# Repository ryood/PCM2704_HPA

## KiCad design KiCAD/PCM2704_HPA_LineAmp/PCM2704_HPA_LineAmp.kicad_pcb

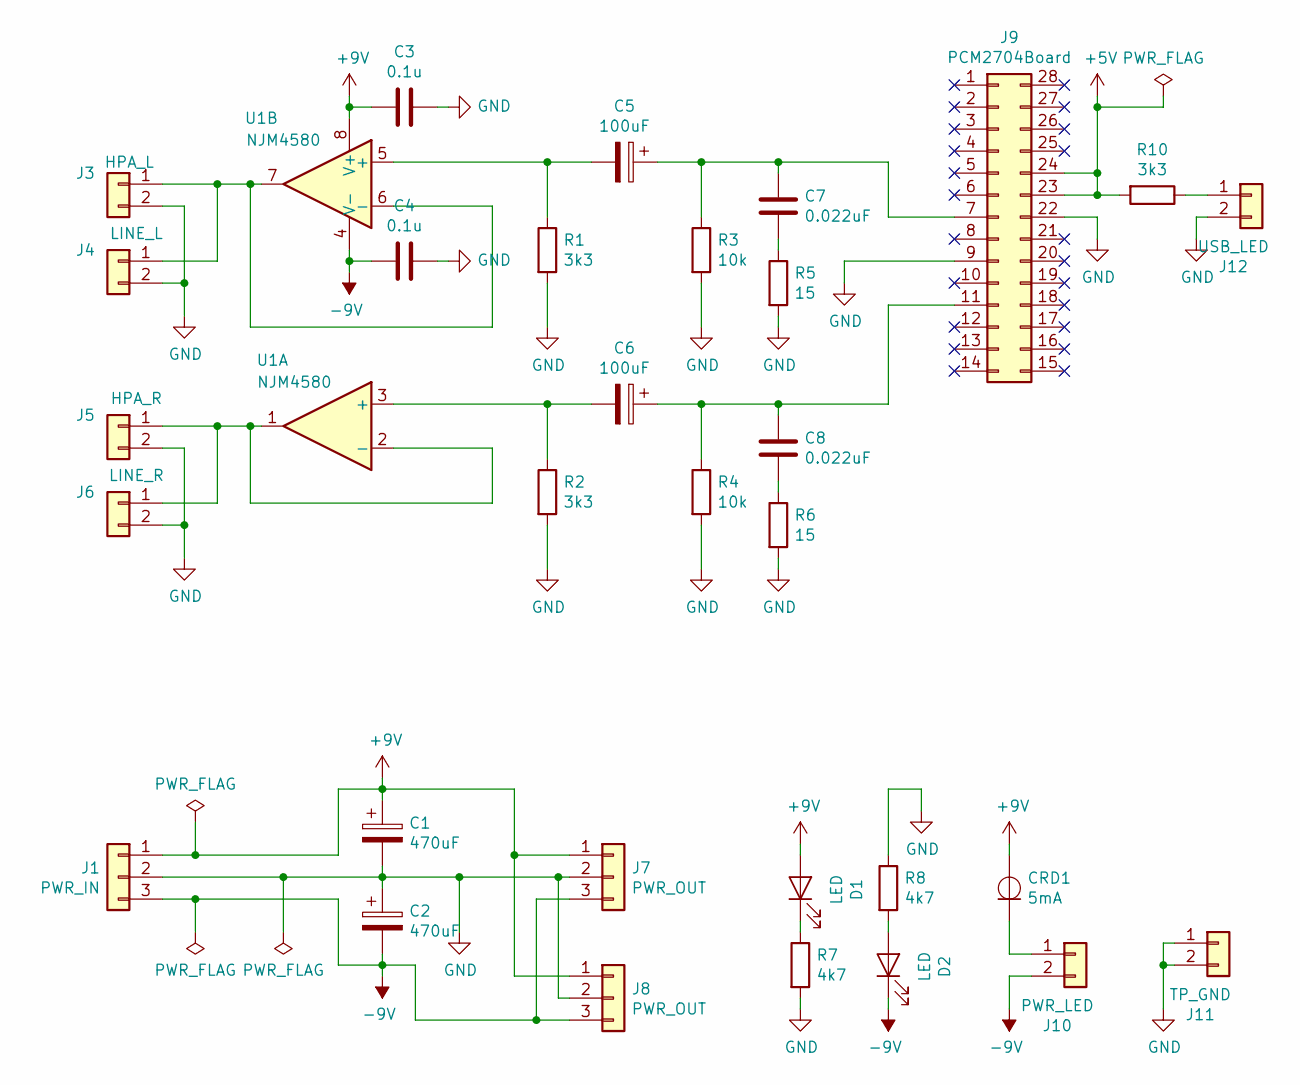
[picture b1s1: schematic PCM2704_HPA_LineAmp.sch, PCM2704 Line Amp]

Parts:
C1, C2: 470uF; CP_Radial_D10.0mm_P5.00mm
C3: 0.1u; C_Disc_D3.0mm_W1.6mm_P2.50mm
C4: 0.1u; C_Disc_D4.3mm_W1.9mm_P5.00mm
C5, C6: 100uF; CP_Radial_D7.5mm_P2.50mm
C7, C8: 0.022uF; C_Rect_L7.0mm_W2.0mm_P5.00mm
CRD1: 5mA; D_DO-35_SOD27_P7.62mm_Horizontal
D1, D2: LED; LED_D3.0mm
J1: PWR_IN; JST_XH_B3B-XH-A_1x03_P2.50mm_Vertical
J3: HPA_L; JST_XH_B2B-XH-A_1x02_P2.50mm_Vertical
J4: LINE_L; JST_XH_B2B-XH-A_1x02_P2.50mm_Vertical
J5: HPA_R; JST_XH_B2B-XH-A_1x02_P2.50mm_Vertical
J6: LINE_R; JST_XH_B2B-XH-A_1x02_P2.50mm_Vertical
J7, J8: PWR_OUT; JST_XH_B3B-XH-A_1x03_P2.50mm_Vertical
J9: PCM2704Board; DIP-28_W15.24mm
J10: PWR_LED; PinHeader_1x02_P2.54mm_Vertical
J11: TP_GND; PinHeader_1x02_P2.54mm_Vertical
J12: USB_LED; PinHeader_1x02_P2.54mm_Vertical
R1, R2, R10: 3k3; R_Axial_DIN0204_L3.6mm_D1.6mm_P7.62mm_Horizontal
R3, R4: 10k; R_Axial_DIN0204_L3.6mm_D1.6mm_P7.62mm_Horizontal
R5, R6: 15; R_Axial_DIN0204_L3.6mm_D1.6mm_P7.62mm_Horizontal
R7, R8: 4k7; R_Axial_DIN0204_L3.6mm_D1.6mm_P7.62mm_Horizontal
U1: NJM4580; DIP-8_W7.62mm_Socket

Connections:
+5V: J9.23, J9.24, R10.2
+9V: C1.1, C3.1, CRD1.2 (A), D1.2 (A), J1.1, J7.1, J8.1, U1.8 (V+)
-9V: C2.2, C4.2, D2.1 (K), J1.3, J7.3, J8.3, J10.2, U1.4 (V-)
GND: C1.2, C2.1, C3.2, C4.1, J1.2, J3.2, J4.2, J5.2, J6.2, J7.2, J8.2, J9.9, J9.22, J11.1, J11.2, J12.2, R1.2, R2.2, R3.2, R4.2, R5.2, R6.2, R7.2, R8.1
unnamed: C5.1, C7.1, J9.7, R3.1
unnamed: C5.2, R1.1, U1.5 (+)
unnamed: C6.1, C8.1, J9.11, R4.1
unnamed: C6.2, R2.1, U1.3 (+)
unnamed: C7.2, R5.1
unnamed: C8.2, R6.1
unnamed: CRD1.1 (K), J10.1
unnamed: D1.1 (K), R7.1
unnamed: D2.2 (A), R8.2
unnamed: J3.1, J4.1, U1.6 (-), U1.7
unnamed: J5.1, J6.1, U1.1, U1.2 (-)
unnamed: J12.1, R10.1

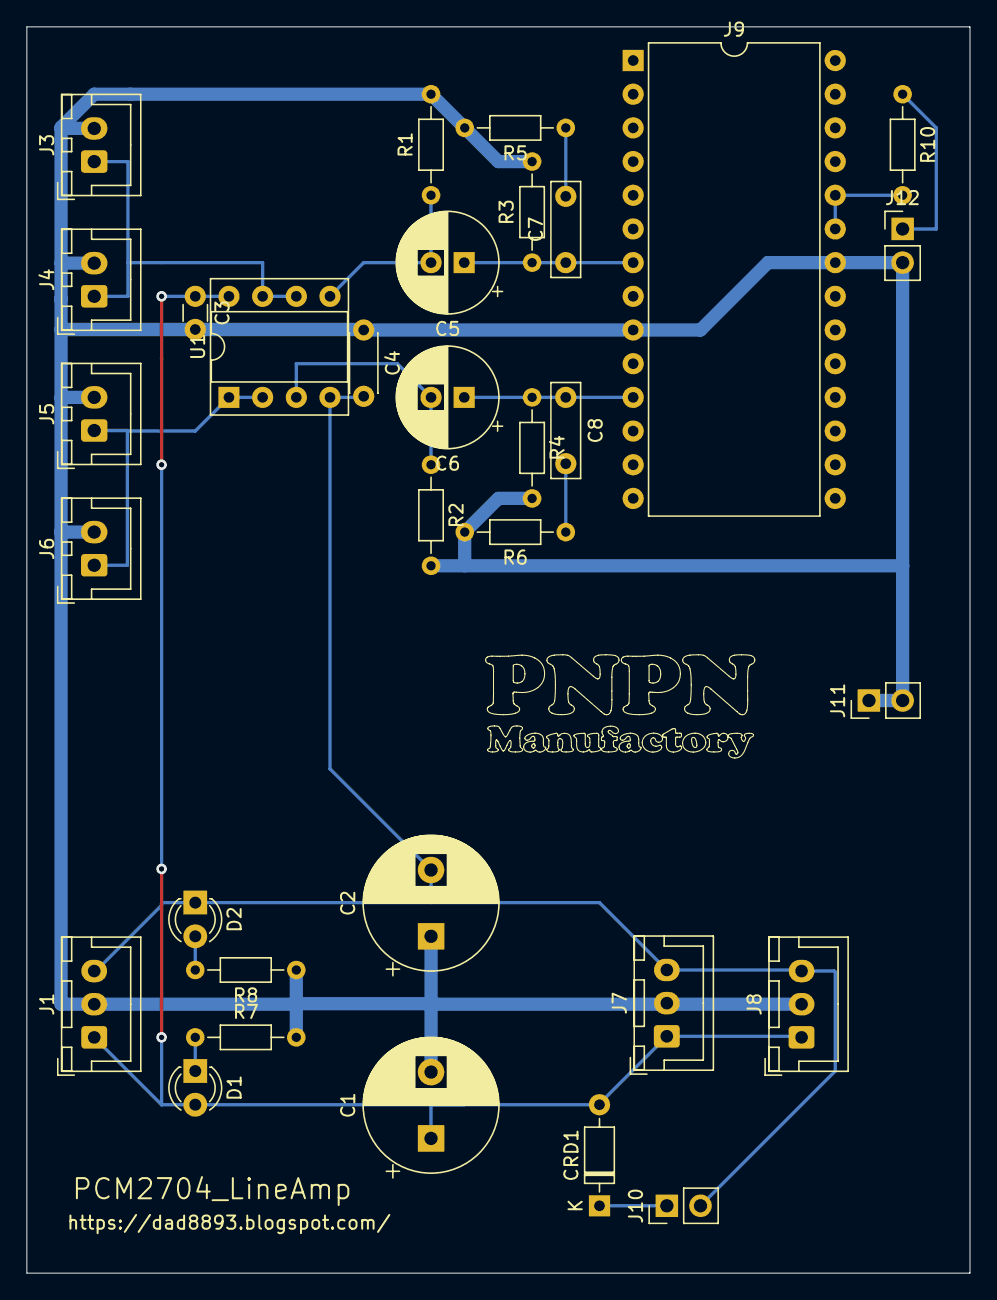
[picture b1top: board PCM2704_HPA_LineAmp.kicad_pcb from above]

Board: 2 copper layers, 71.1 x 94.0 mm, 32 parts (0 on the bottom side), 16 nets.

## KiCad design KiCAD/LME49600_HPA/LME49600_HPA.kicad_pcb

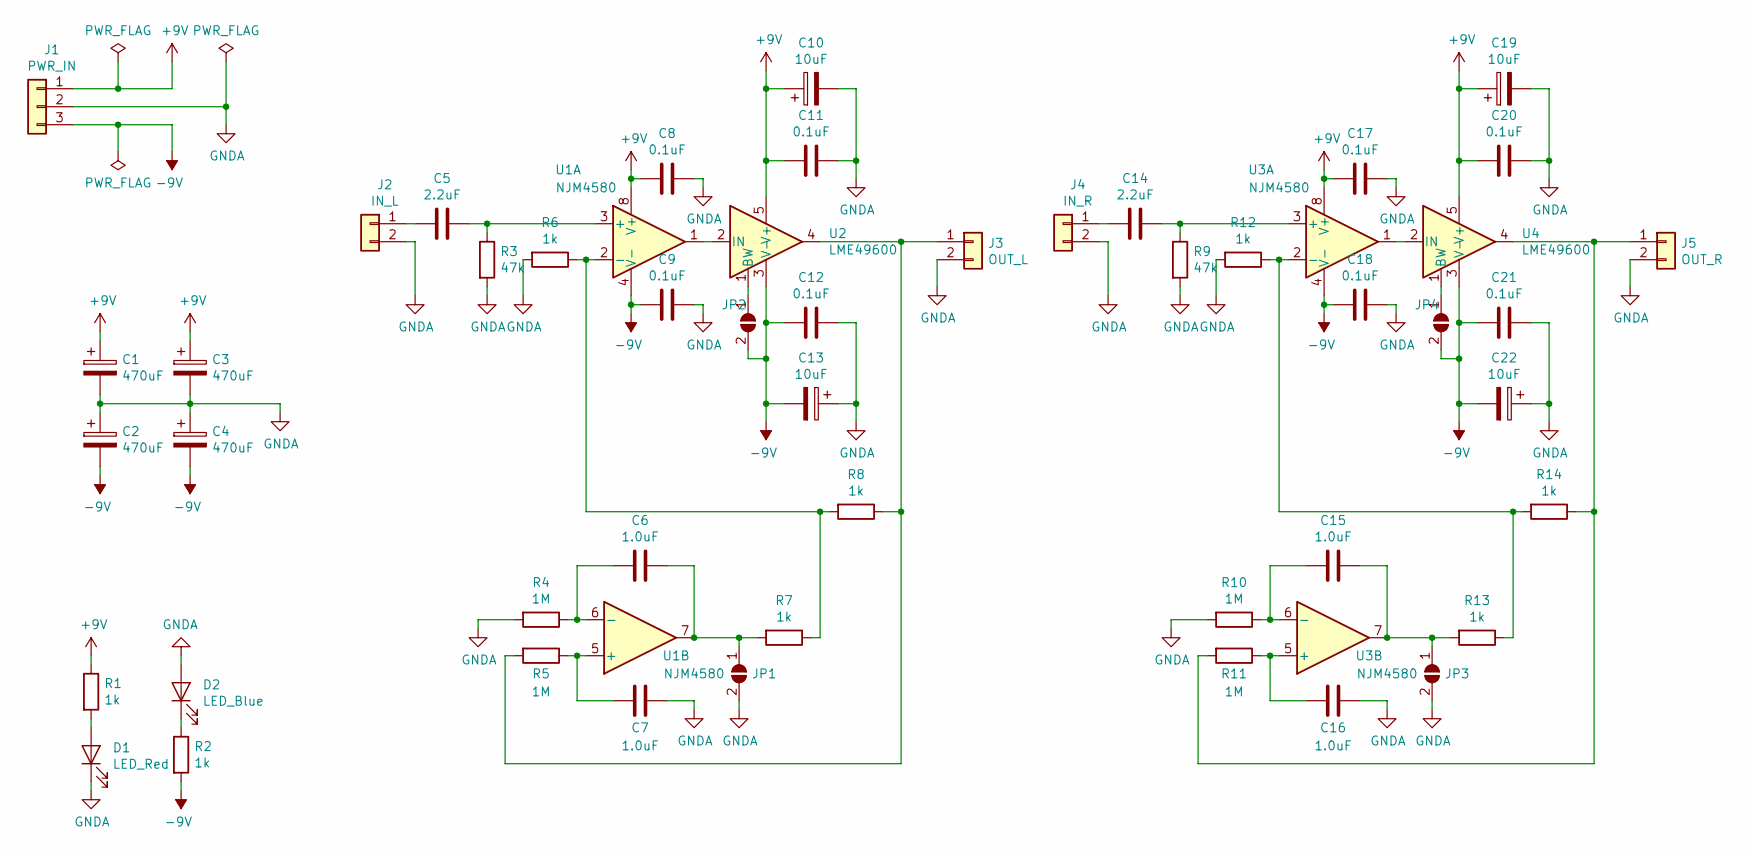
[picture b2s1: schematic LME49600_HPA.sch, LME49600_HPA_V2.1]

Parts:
C1, C2, C3, C4: 470uF; CP_Radial_D17.0mm_P7.50mm
C5, C14: 2.2uF; C_Rect_L7.2mm_W7.2mm_P5.00mm_FKS2_FKP2_MKS2_MKP2
C6, C7, C15, C16: 1.0uF; C_Rect_L7.2mm_W5.5mm_P5.00mm_FKS2_FKP2_MKS2_MKP2
C8, C9, C11, C12, C17, C18, C20, C21: 0.1uF; C_Rect_L4.6mm_W2.0mm_P2.50mm_MKS02_FKP02
C10, C13, C19, C22: 10uF; CP_Radial_D6.3mm_P2.50mm
D1: LED_Red; LED_D3.0mm
D2: LED_Blue; LED_D3.0mm
J1: PWR_IN; JST_XH_B3B-XH-A_1x03_P2.50mm_Vertical
J2: IN_L; JST_XH_B2B-XH-A_1x02_P2.50mm_Vertical
J3: OUT_L; JST_XH_B2B-XH-A_1x02_P2.50mm_Vertical
J4: IN_R; JST_XH_B2B-XH-A_1x02_P2.50mm_Vertical
J5: OUT_R; JST_XH_B2B-XH-A_1x02_P2.50mm_Vertical
JP1, JP2, JP3, JP4: SolderJumper_2_Open; SolderJumper-2_P1.3mm_Open_RoundedPad1.0x1.5mm
R1, R2, R6, R7, R8, R12, R13, R14: 1k; R_Axial_DIN0207_L6.3mm_D2.5mm_P7.62mm_Horizontal
R3, R9: 47k; R_Axial_DIN0207_L6.3mm_D2.5mm_P7.62mm_Horizontal
R4, R5, R10, R11: 1M; R_Axial_DIN0207_L6.3mm_D2.5mm_P7.62mm_Horizontal
U1, U3: NJM4580; DIP-8_W7.62mm_Socket_LongPads
U2, U4: LME49600; TO-263-5_TabPin3

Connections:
+9V: C1.1, C3.1, C8.2, C10.1, C11.2, C17.2, C19.1, C20.2, J1.1, R1.1, U1.8 (V+), U2.5 (V+), U3.8 (V+), U4.5 (V+)
-9V: C2.2, C4.2, C9.2, C12.2, C13.2, C18.2, C21.2, C22.2, J1.3, JP2.2 (B), JP4.2 (B), R2.2, U1.4 (V-), U2.3 (V-), U3.4 (V-), U4.3 (V-)
GNDA: C1.2, C2.1, C3.2, C4.1, C7.1, C8.1, C9.1, C10.2, C11.1, C12.1, C13.1, C16.1, C17.1, C18.1, C19.2, C20.1, C21.1, C22.1, D1.1 (K), D2.2 (A), J1.2, J2.2, J3.2, J4.2, J5.2, JP1.2 (B), JP3.2 (B), R3.2, R4.2, R6.2, R9.2, R10.2, R12.2
unnamed: C5.1, R3.1, U1.3 (+)
unnamed: C5.2, J2.1
unnamed: C6.1, JP1.1 (A), R7.2, U1.7
unnamed: C6.2, R4.1, U1.6 (-)
unnamed: C7.2, R5.1, U1.5 (+)
unnamed: C14.1, R9.1, U3.3 (+)
unnamed: C14.2, J4.1
unnamed: C15.1, JP3.1 (A), R13.2, U3.7
unnamed: C15.2, R10.1, U3.6 (-)
unnamed: C16.2, R11.1, U3.5 (+)
unnamed: D1.2 (A), R1.2
unnamed: D2.1 (K), R2.1
unnamed: J3.1, R5.2, R8.1, U2.4
unnamed: J5.1, R11.2, R14.1, U4.4
unnamed: JP2.1 (A), U2.1 (BW)
unnamed: JP4.1 (A), U4.1 (BW)
unnamed: R6.1, R7.1, R8.2, U1.2 (-)
unnamed: R12.1, R13.1, R14.2, U3.2 (-)
unnamed: U1.1, U2.2 (IN)
unnamed: U3.1, U4.2 (IN)

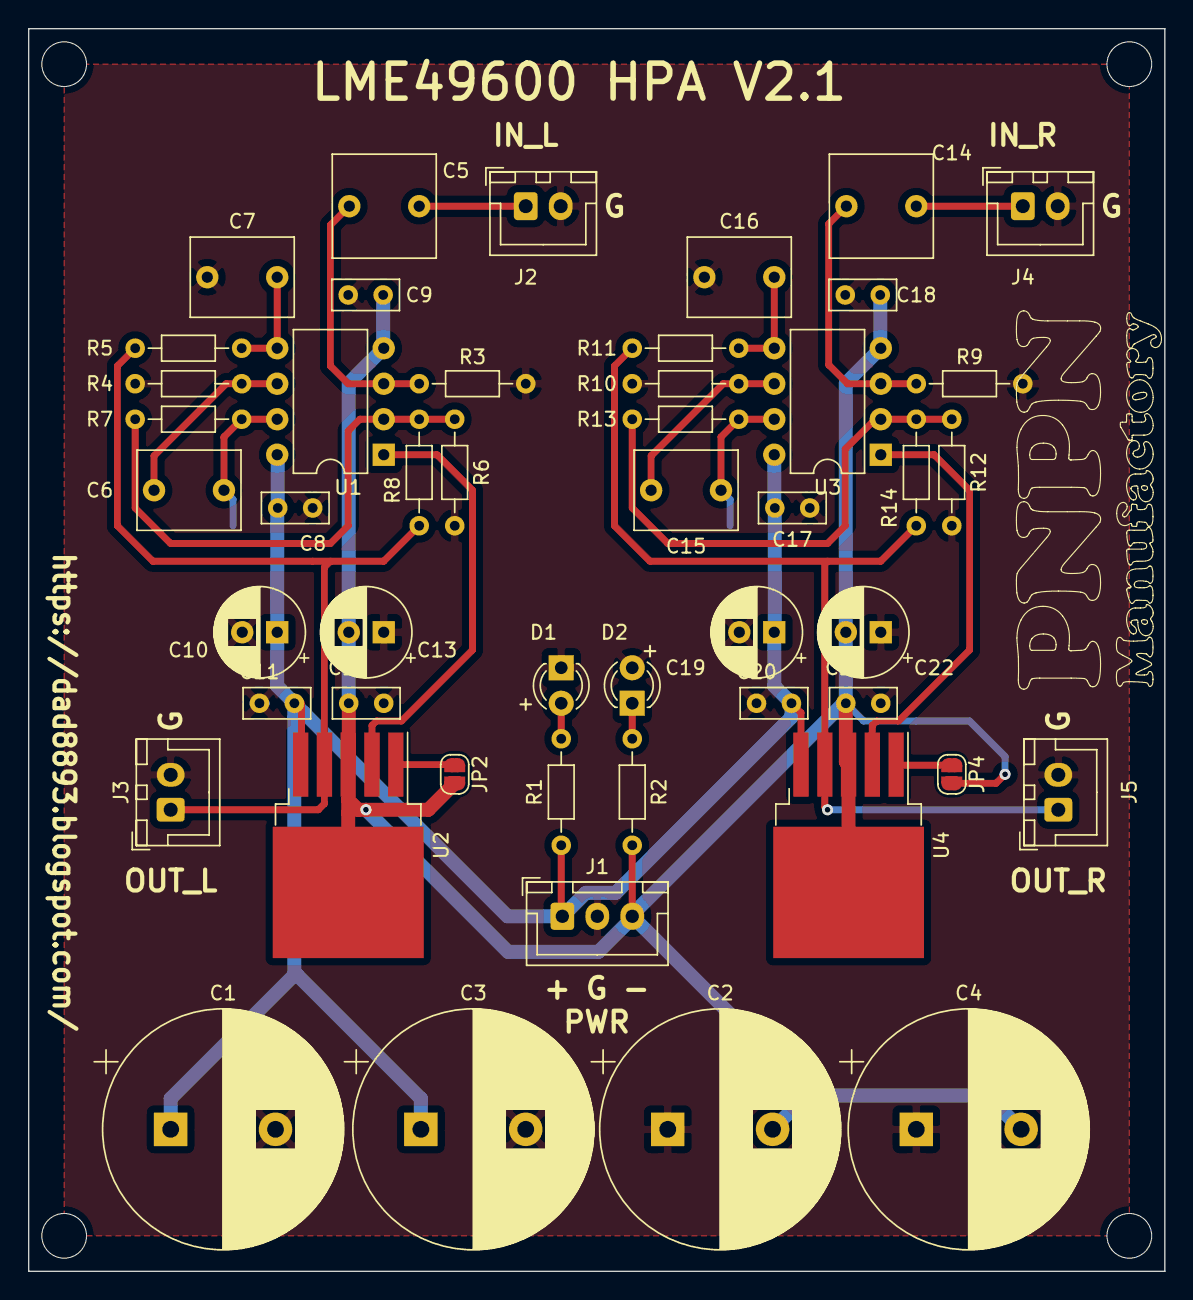
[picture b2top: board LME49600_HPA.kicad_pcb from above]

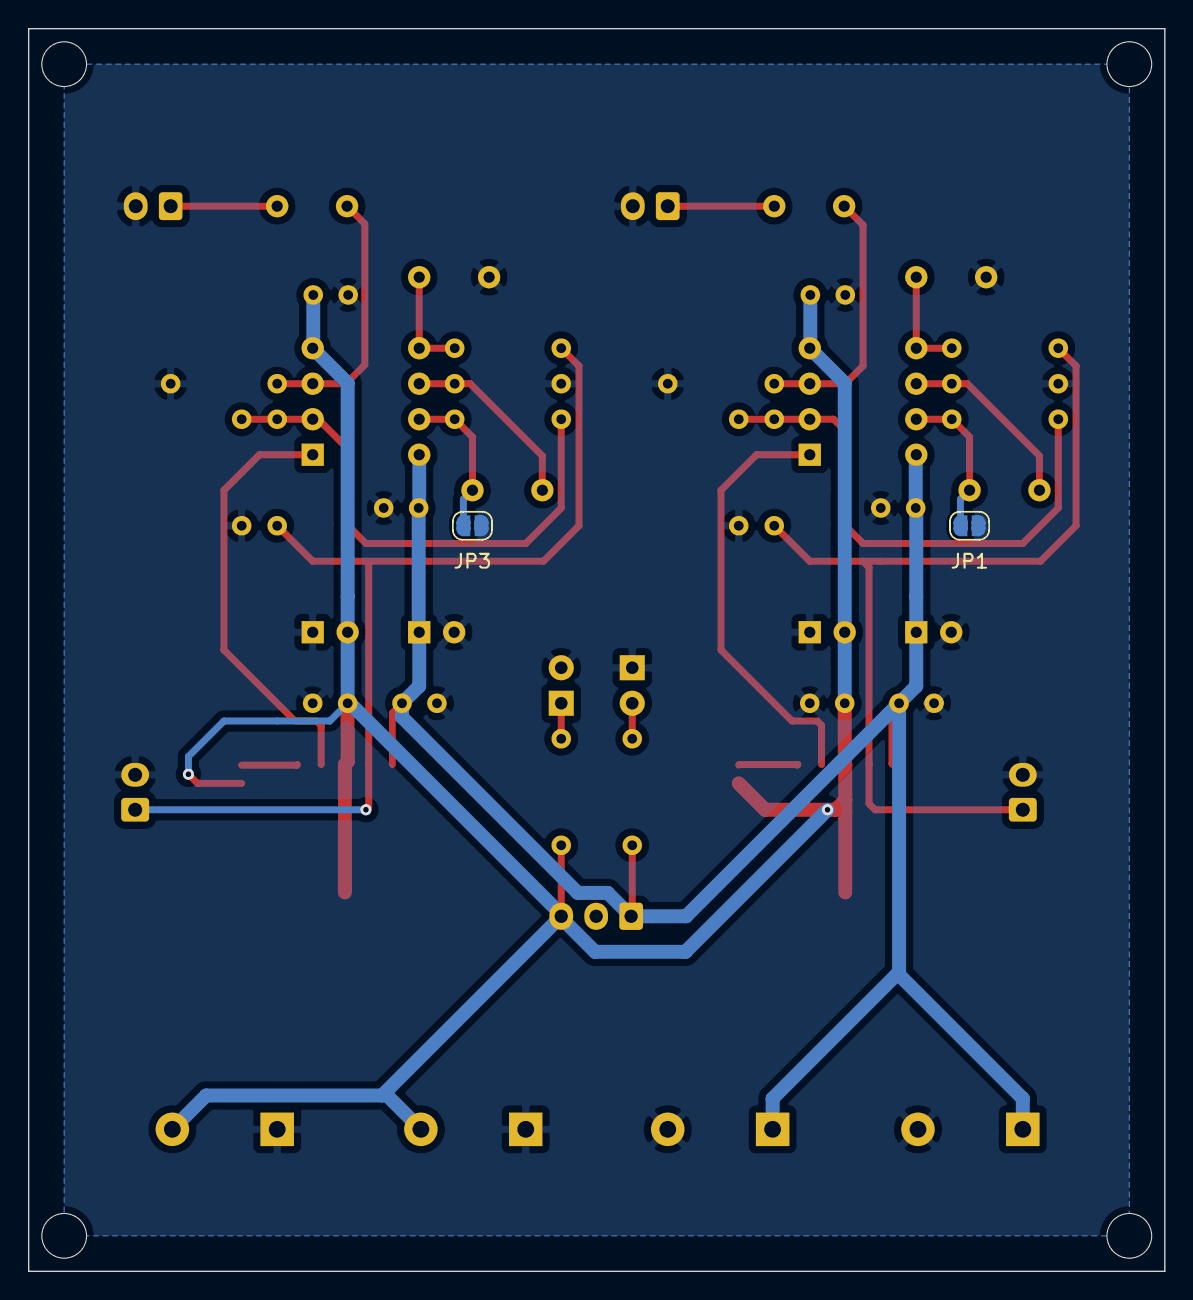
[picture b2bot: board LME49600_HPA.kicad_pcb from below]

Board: 2 copper layers, 81.3 x 88.9 mm, 51 parts (2 on the bottom side), 23 nets.

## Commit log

2019-10-15 Add: LME49600_HPA KiCAD files.
2019-10-29 Add: PCM2704 HPA ブロック図.xlsx
2019-10-29 Update: PCM2704 HPA ブロック図.xlsx
2019-11-08 Add: PCM2704_LineAmp
2019-11-09 Update: PCM2704_HPA_LineAmp board design
2019-11-29 Add: Case design
2020-01-03 Update: Case design
2020-01-26 Add: テスト表
